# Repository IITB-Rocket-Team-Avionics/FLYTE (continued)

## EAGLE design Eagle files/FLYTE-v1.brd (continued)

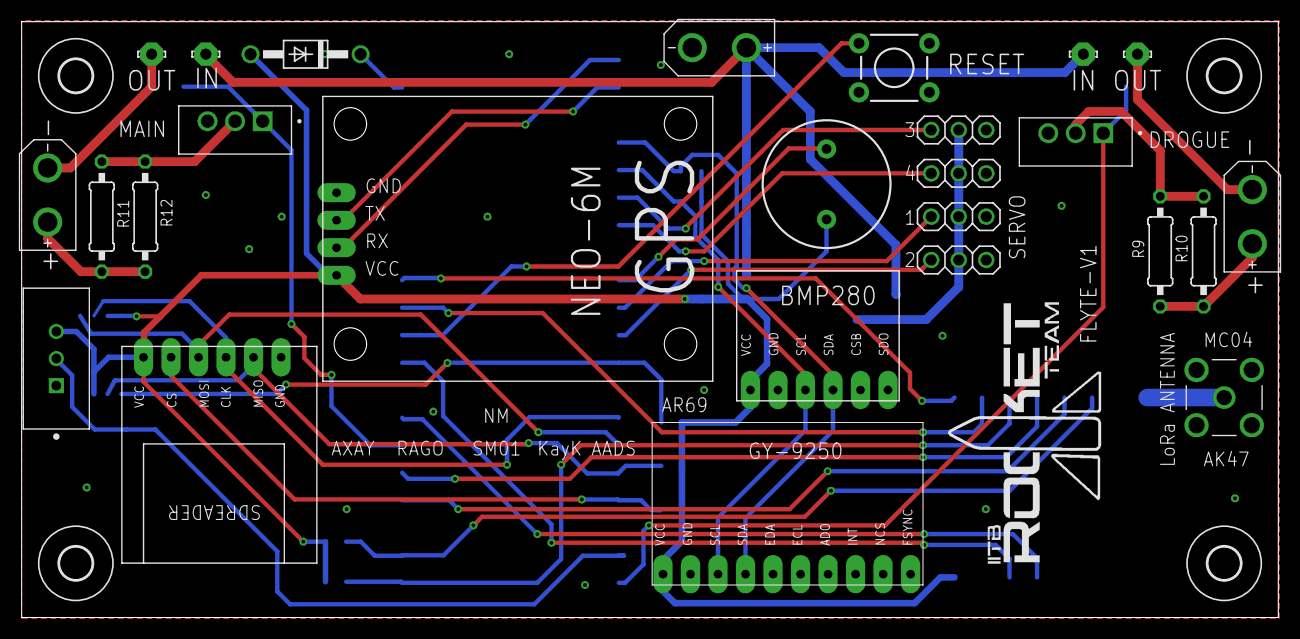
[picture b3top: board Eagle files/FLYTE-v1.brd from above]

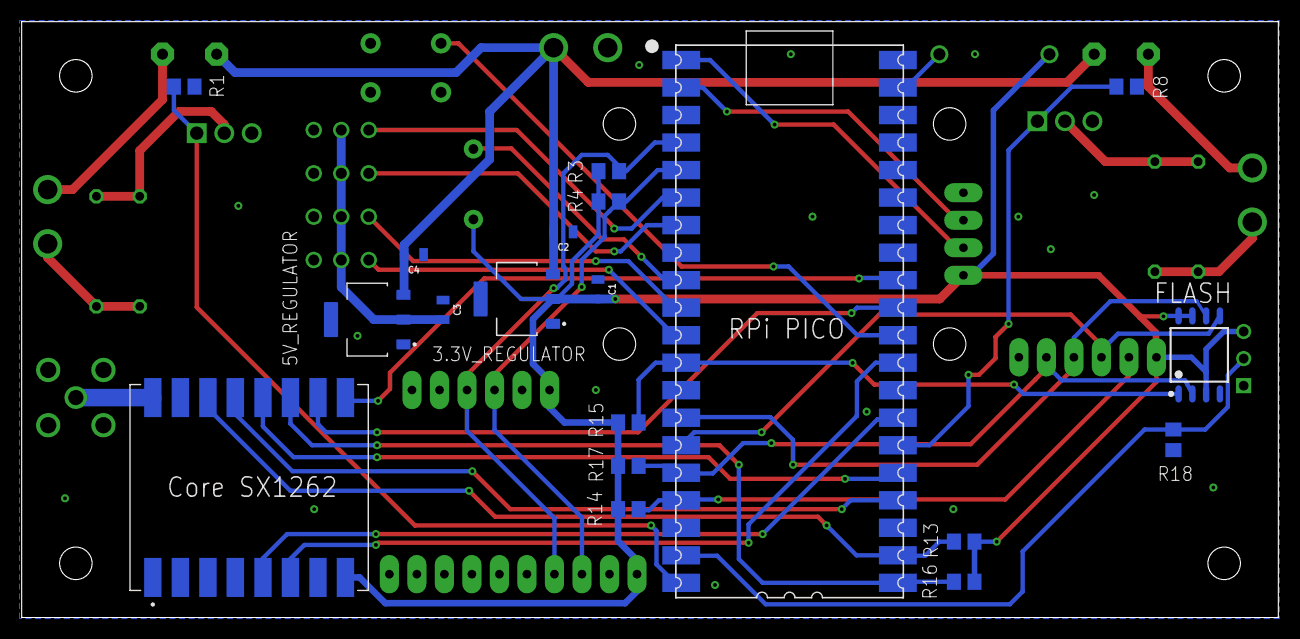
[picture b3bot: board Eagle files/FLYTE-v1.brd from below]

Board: 2 copper layers, 116.0 x 55.0 mm, 49 parts (19 on the bottom side), 38 nets.

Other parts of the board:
U$5, U$6, U$7, U$8: 3,0

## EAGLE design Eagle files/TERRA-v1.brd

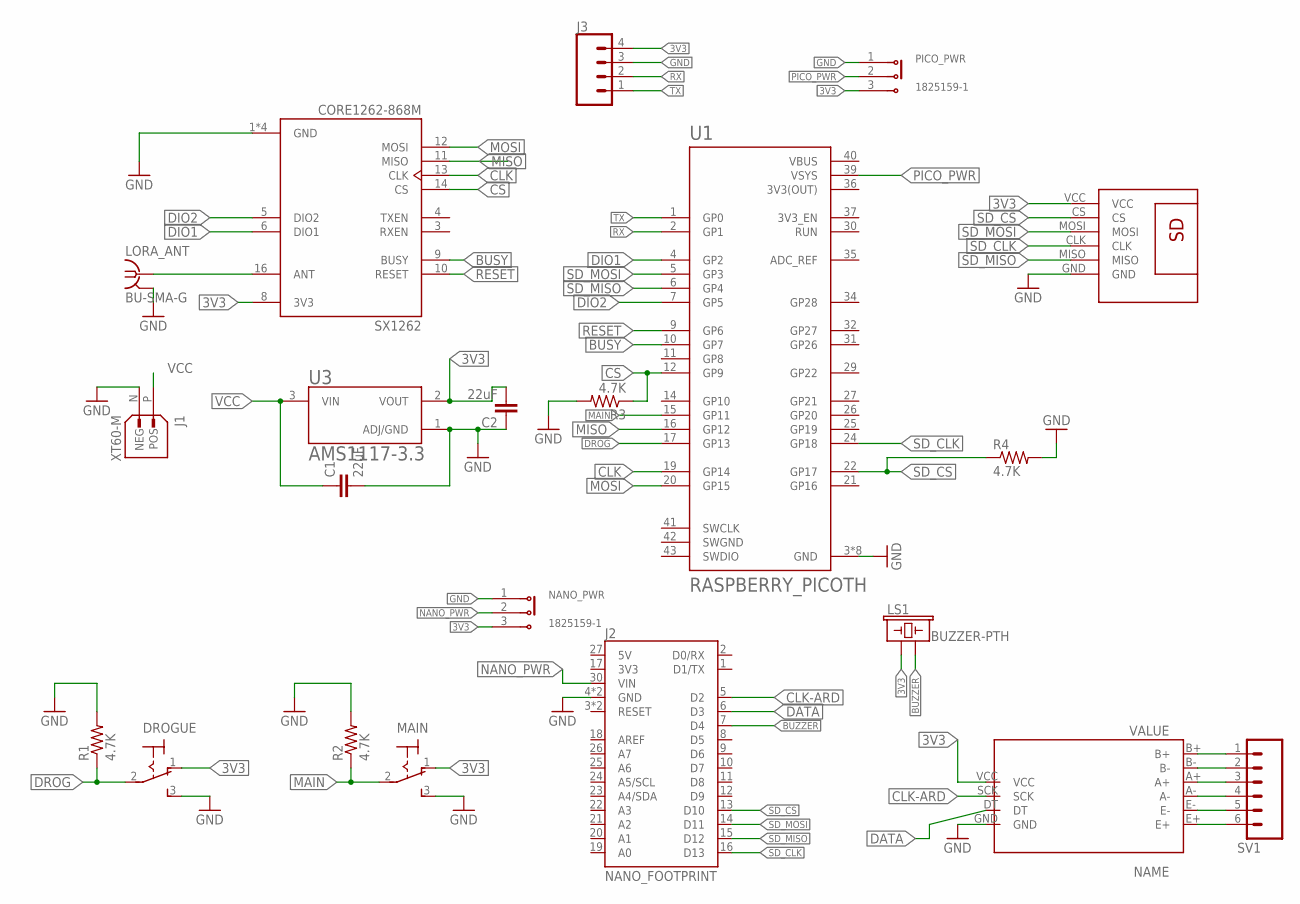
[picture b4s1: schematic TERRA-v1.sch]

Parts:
C1, C2: 22uF; 0805
DROGUE: M9040P
HX711: HX711
J1: XT60-M; AMASS_XT60-M
J2: NANO_FOOTPRINT; NANO
J3: CONN_04PTH; 1X04
LORA_ANT: BU-SMA-G
LS1: BUZZER-PTH; BUZZER-12MM
MAIN: M9040P
NANO_PWR: 1825159-1; SW_1825159-1
PICO_PWR: 1825159-1; SW_1825159-1
R1, R2, R3, R4: 4.7K; R0805
SV1: CONN_06SILK_FEMALE_PTH; 1X06
SX1262: CORE1262-868M; XCVR_CORE1262-868M
U1: RASPBERRY_PICOTH; PICO-PKG-TH
U3: AMS1117-3.3; SOT229P700X180-4N
U$1: SDREADER

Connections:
3V3: C2.2, DROGUE.1 (O), HX711.VCC, J3.4, LS1.+ (1), MAIN.1 (O), NANO_PWR.3, PICO_PWR.3, SX1262.8 (3V3), U3.2 (VOUT), U$1.VCC
3V3(OUT): U1.36 (3V3(OUT))
BUSY: SX1262.9 (BUSY), U1.10 (GP7)
BUZZER: J2.7 (D4), LS1.- (2)
CLK: SX1262.13 (CLK), U1.19 (GP14)
CLK-ARD: HX711.SCK, J2.5 (D2)
CS: R3.1, SX1262.14 (CS), U1.12 (GP9)
DATA: HX711.DT, J2.6 (D3)
DIO1: SX1262.6 (DIO1), U1.4 (GP2)
DIO2: SX1262.5 (DIO2), U1.7 (GP5)
DROG: DROGUE.2, R1.1, U1.17 (GP13)
GND: C1.2, C2.1, DROGUE.3 (S), HX711.GND, J1.N (NEG), J2.4 (GND), J2.29 (GND), J3.3, LORA_ANT.2, LORA_ANT.3 (2), LORA_ANT.4 (2), LORA_ANT.5 (2), MAIN.3 (S), NANO_PWR.1, PICO_PWR.1, R1.2, R2.2, R3.2, R4.2, SX1262.1 (GND), SX1262.2 (GND), SX1262.7 (GND), SX1262.15 (GND), U1.3 (GND), U1.8 (GND), U1.13 (GND), U1.18 (GND), U1.23 (GND), U1.28 (GND), U1.33 (GND), U1.38 (GND), U3.1 (ADJ/GND), U$1.GND
MAIN: MAIN.2, R2.1, U1.15 (GP11)
MISO: SX1262.11 (MISO), U1.16 (GP12)
MOSI: SX1262.12 (MOSI), U1.20 (GP15)
unnamed: LORA_ANT.1, SX1262.16 (ANT)
unnamed: HX711.B+, SV1.1
unnamed: HX711.B-, SV1.2
unnamed: HX711.A+, SV1.3
unnamed: HX711.A-, SV1.4
unnamed: HX711.E-, SV1.5
unnamed: HX711.E+, SV1.6
NANO_PWR: J2.30 (VIN), NANO_PWR.2
PICO_PWR: PICO_PWR.2, U1.39 (VSYS)
RESET: SX1262.10 (RESET), U1.9 (GP6)
RX: J3.2, U1.2 (GP1)
SD_CLK: J2.16 (D13), U1.24 (GP18), U$1.CLK
SD_CS: J2.13 (D10), R4.1, U1.22 (GP17), U$1.CS
SD_MISO: J2.15 (D12), U1.6 (GP4), U$1.MISO
SD_MOSI: J2.14 (D11), U1.5 (GP3), U$1.MOSI
SWGND: U1.42 (SWGND)
TX: J3.1, U1.1 (GP0)
VBUS: U1.40 (VBUS)
VCC: C1.1, J1.P (POS), U3.3 (VIN)

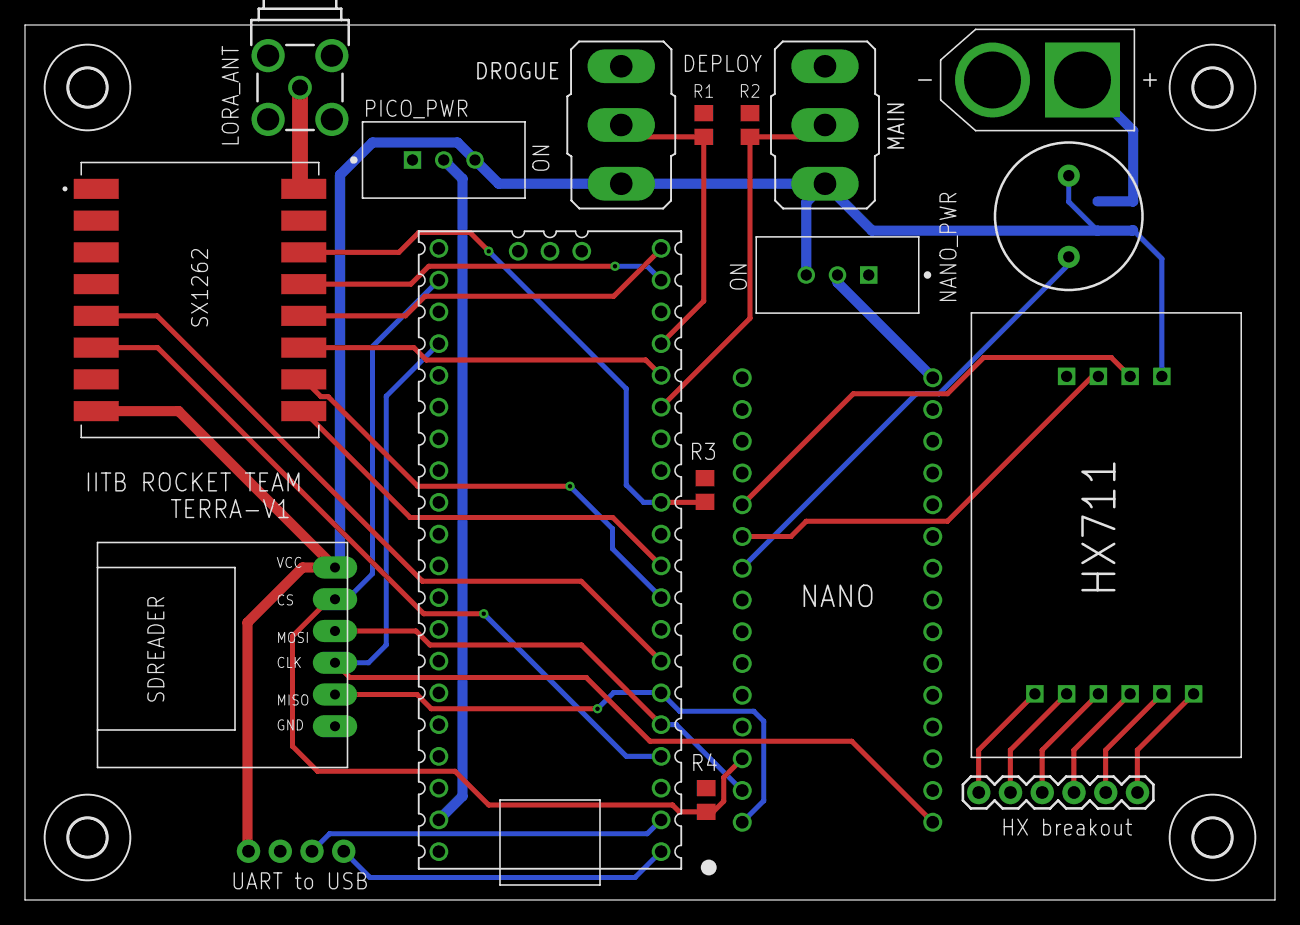
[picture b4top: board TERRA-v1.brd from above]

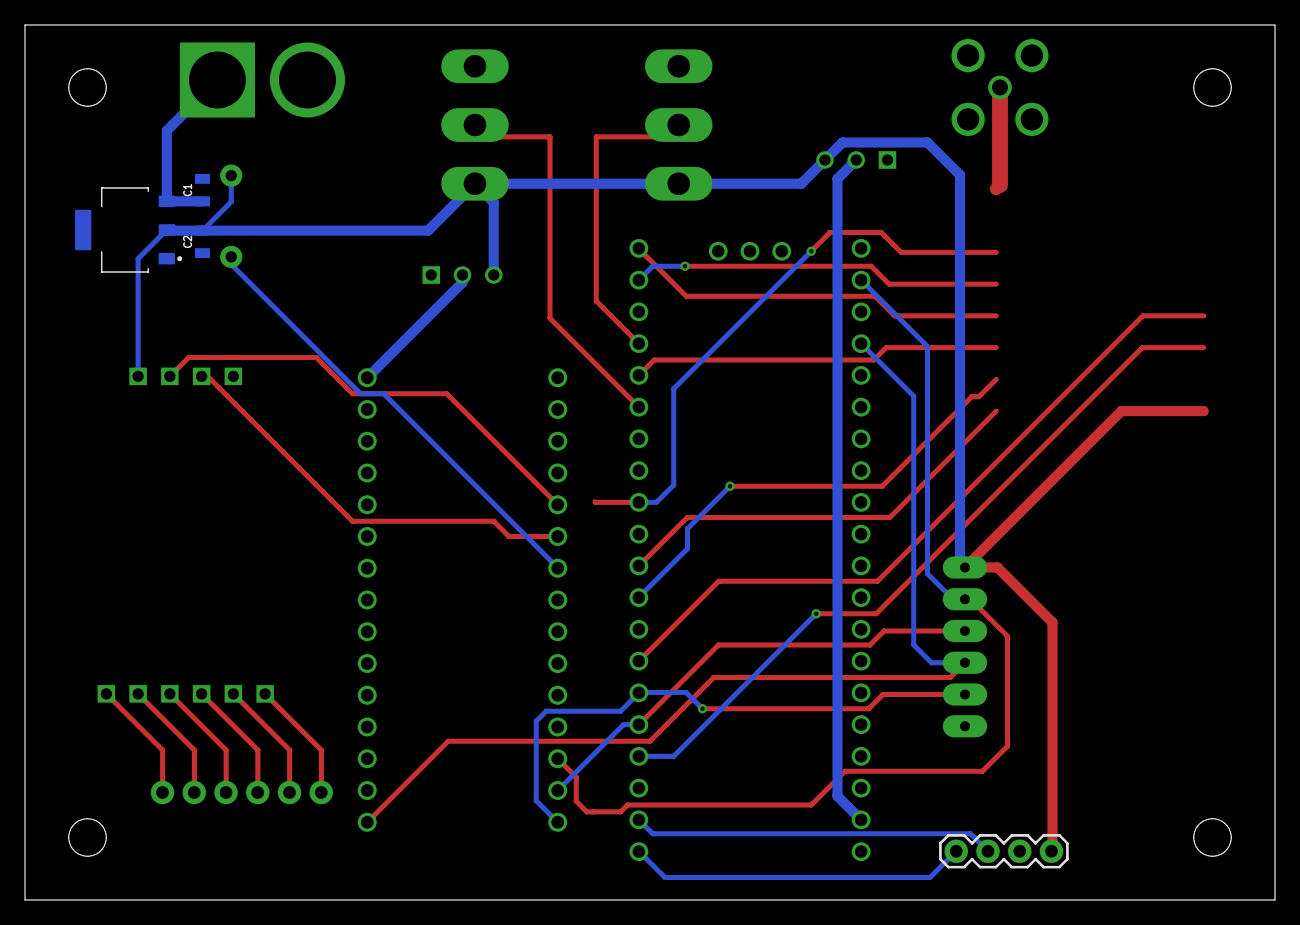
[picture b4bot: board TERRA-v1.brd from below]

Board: 2 copper layers, 100.0 x 70.0 mm, 25 parts (4 on the bottom side), 31 nets.

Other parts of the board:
U$3, U$4, U$5, U$6: 3,0

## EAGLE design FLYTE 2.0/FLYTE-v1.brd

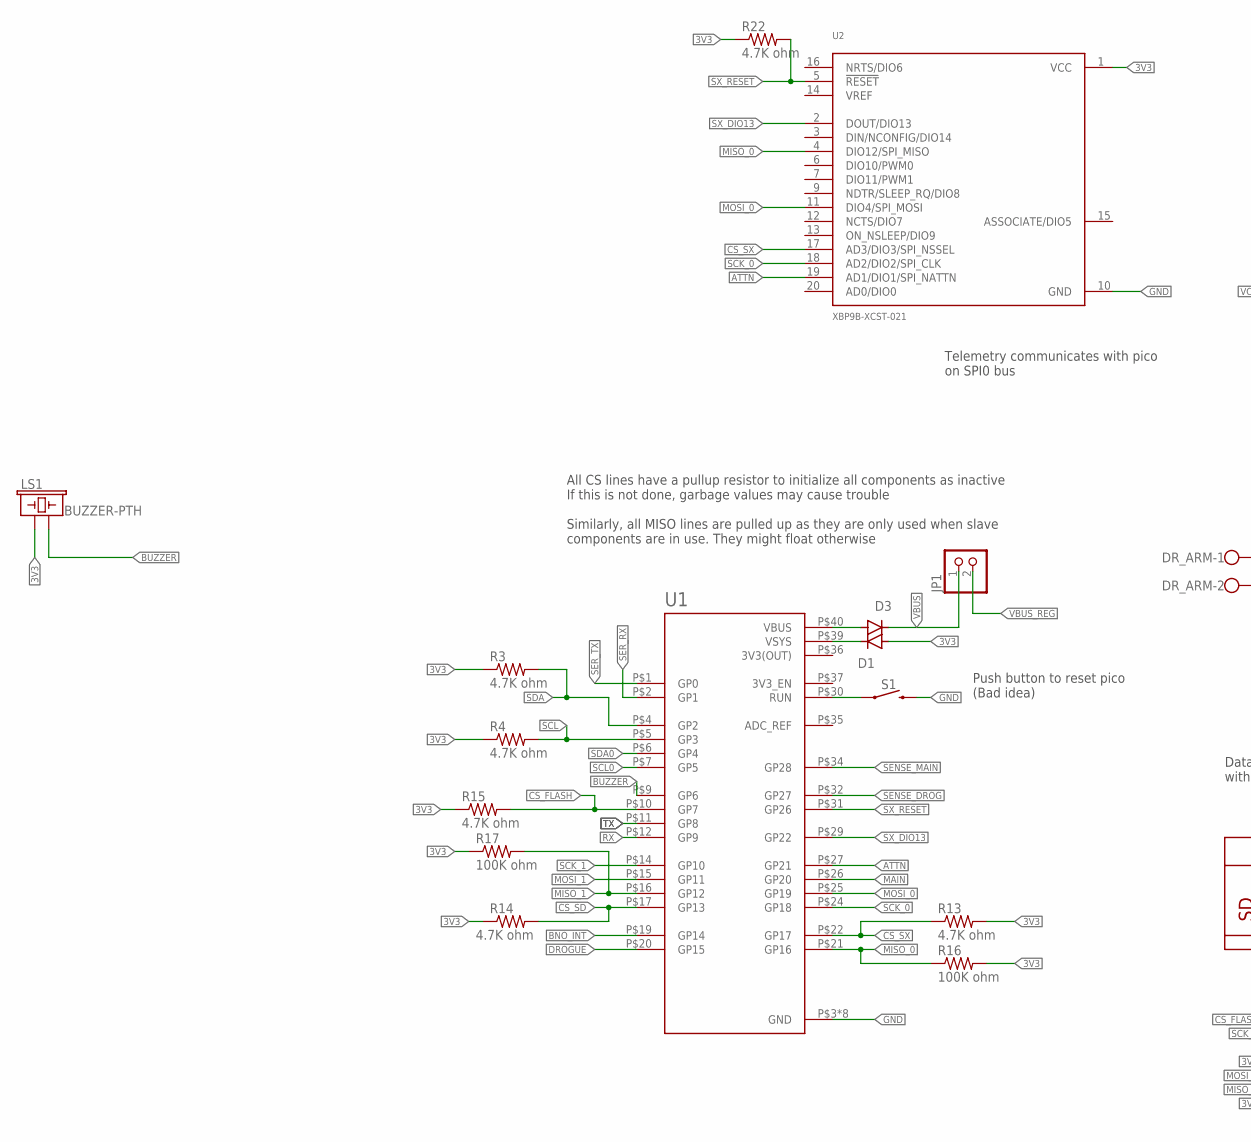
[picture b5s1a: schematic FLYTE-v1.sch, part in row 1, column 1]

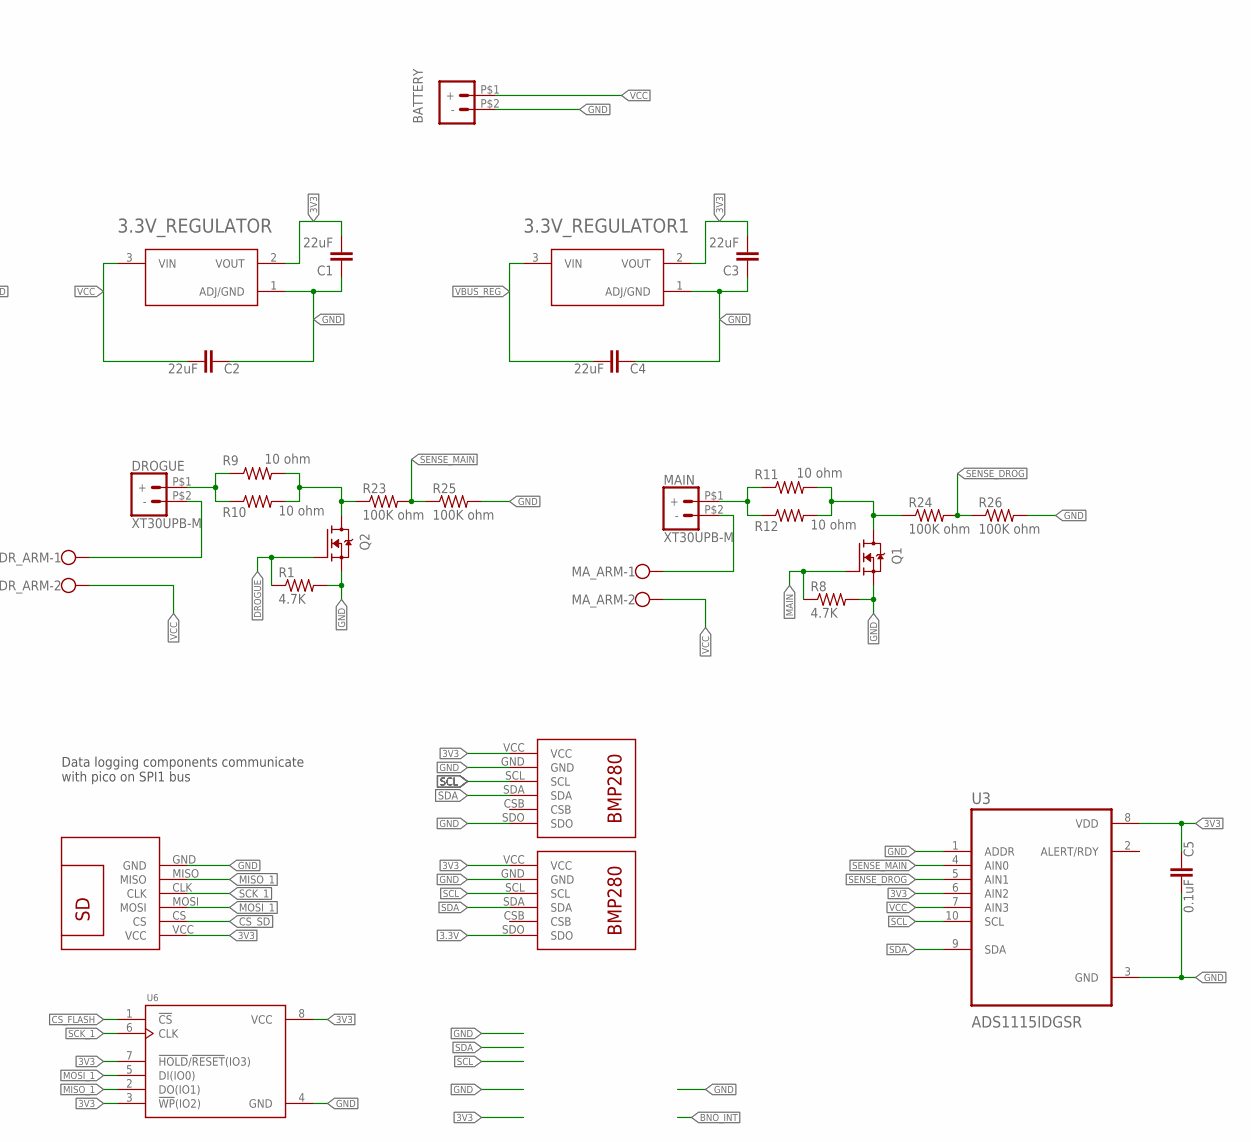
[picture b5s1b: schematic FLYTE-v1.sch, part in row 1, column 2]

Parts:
3.3V_REGULATOR, 3.3V_REGULATOR1: AMS1117-3.3; SOT229P700X180-4N
BATTERY: XT30UPB-M
C1, C2, C3, C4: 22uF; 0805
C5: 0.1uF; 0805
D1, D3: 1N4004; DO41-10
DROGUE: XT30UPB-M
DR_ARM: W237-102
JP1: PINHD-1X2; 1X02
LS1: BUZZER-PTH; BUZZER-12MM
MAIN: XT30UPB-M
MA_ARM: W237-102
Q1, Q2: IRF540NPBF; TO254P1054X469X1930-3
R1, R8: 4.7K; R0805
R3, R4, R13, R14, R15, R22: 4.7K ohm; R0805
R9, R10, R11, R12: 10 ohm; 0207/10
R16, R17, R23, R24, R25, R26: 100K ohm; R0805
S1: MOMENTARY-SWITCH-SPST-PTH-6.0MM; TACTILE_SWITCH_PTH_6.0MM
U1: RASPBERRY_PICO-NO_DEBUG; PICO-PKG-NO_DEBUG
U2: XBP9B-XCST-021; DIP2200W51P200L3294H279Q20P
U3: ADS1115IDGSR; SOP50P490X110-10N
U6: W25Q32JVSSIQ; SOIC127P790X216-8N
U$1, U$2: BMP280
U$3: SDREADER

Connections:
3.3V: U$2.SDO
3V3: 3.3V_REGULATOR.2 (VOUT), 3.3V_REGULATOR1.2 (VOUT), C1.2, C3.2, C5.1, D1.A, LS1.+ (1), R3.1, R4.1, R13.2, R14.1, R15.1, R16.2, R17.1, R22.1, U2.1 (VCC), U3.6 (AIN2), U3.8 (VDD), U6.3 (!WP!(IO2)), U6.7 (!HOLD!/!RESET!(IO3)), U6.8 (VCC), U$1.VCC, U$2.VCC, U$3.VCC
3V3(OUT): U1.P$36 (3V3(OUT))
ATTN: U1.P$27 (GP21), U2.19 (AD1/DIO1/SPI_NATTN)
BNO_INT: U1.P$19 (GP14)
BUZZER: LS1.- (2), U1.P$9 (GP6)
CS_FLASH: R15.2, U1.P$10 (GP7), U6.1 (!CS)
CS_SD: R14.2, U1.P$17 (GP13), U$3.CS
CS_SX: R13.1, U1.P$22 (GP17), U2.17 (AD3/DIO3/SPI_NSSEL)
DROGUE: Q2.1 (G), R1.1, U1.P$20 (GP15)
GND: 3.3V_REGULATOR.1 (ADJ/GND), 3.3V_REGULATOR1.1 (ADJ/GND), BATTERY.P$2 (-), C1.1, C2.1, C3.1, C4.1, C5.2, Q1.3 (S), Q2.3 (S), R1.2, R8.2, R25.2, R26.2, S1.3 (2), U1.P$3 (GND), U1.P$8 (GND), U1.P$13 (GND), U1.P$18 (GND), U1.P$23 (GND), U1.P$28 (GND), U1.P$33 (GND), U1.P$38 (GND), U2.10 (GND), U3.1 (ADDR), U3.3 (GND), U6.4 (GND), U$1.GND, U$1.SDO, U$2.GND, U$3.GND
MAIN: Q1.1 (G), R8.1, U1.P$26 (GP20)
MISO_0: R16.1, U1.P$21 (GP16), U2.4 (DIO12/SPI_MISO)
MISO_1: R17.2, U1.P$16 (GP12), U6.2 (DO(IO1)), U$3.MISO
MOSI_0: U1.P$25 (GP19), U2.11 (DIO4/SPI_MOSI)
MOSI_1: U1.P$15 (GP11), U6.5 (DI(IO0)), U$3.MOSI
unnamed: D1.C, U1.P$39 (VSYS)
unnamed: DROGUE.P$2 (-), DR_ARM.1
unnamed: MAIN.P$1 (+), R11.1, R12.1
unnamed: DROGUE.P$1 (+), R9.1, R10.1
unnamed: S1.1, U1.P$30 (RUN)
unnamed: Q2.2 (D), R9.2, R10.2, R23.1
unnamed: Q1.2 (D), R11.2, R12.2, R24.1
unnamed: MAIN.P$2 (-), MA_ARM.1
unnamed: D3.A, U1.P$40 (VBUS)
RX: U1.P$12 (GP9)
SCK_0: U1.P$24 (GP18), U2.18 (AD2/DIO2/SPI_CLK)
SCK_1: U1.P$14 (GP10), U6.6 (CLK), U$3.CLK
SCL: R4.2, U1.P$5 (GP3), U3.10 (SCL), U$1.SCL, U$2.SCL
SCL0: U1.P$7 (GP5)
SDA: R3.2, U1.P$4 (GP2), U3.9 (SDA), U$1.SDA, U$2.SDA
SDA0: U1.P$6 (GP4)
SENSE_DROG: R24.2, R26.1, U1.P$32 (GP27), U3.5 (AIN1)
SENSE_MAIN: R23.2, R25.1, U1.P$34 (GP28), U3.4 (AIN0)
SER_RX: U1.P$2 (GP1)
SER_TX: U1.P$1 (GP0)
SX_DIO13: U1.P$29 (GP22), U2.2 (DOUT/DIO13)
SX_RESET: R22.2, U1.P$31 (GP26), U2.5 (!RESET)
TX: U1.P$11 (GP8)
VBUS: D3.C, JP1.1
VBUS_REG: 3.3V_REGULATOR1.3 (VIN), C4.2, JP1.2
VCC: 3.3V_REGULATOR.3 (VIN), BATTERY.P$1 (+), C2.2, DR_ARM.2, MA_ARM.2, U3.7 (AIN3)

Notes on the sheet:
Telemetry communicates with pico on SPI0 bus
Data logging components communicate with pico on SPI1 bus
All CS lines have a pullup resistor to initialize all components as inactive If this is not done, garbage values may cause trouble Similarly, all MISO lines are pulled up as they are only used when slave components are in use. They might float otherwise
Push button to reset pico (Bad idea)

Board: 2 copper layers, 44 parts (0 on the bottom side), 33 nets, no tracks yet.

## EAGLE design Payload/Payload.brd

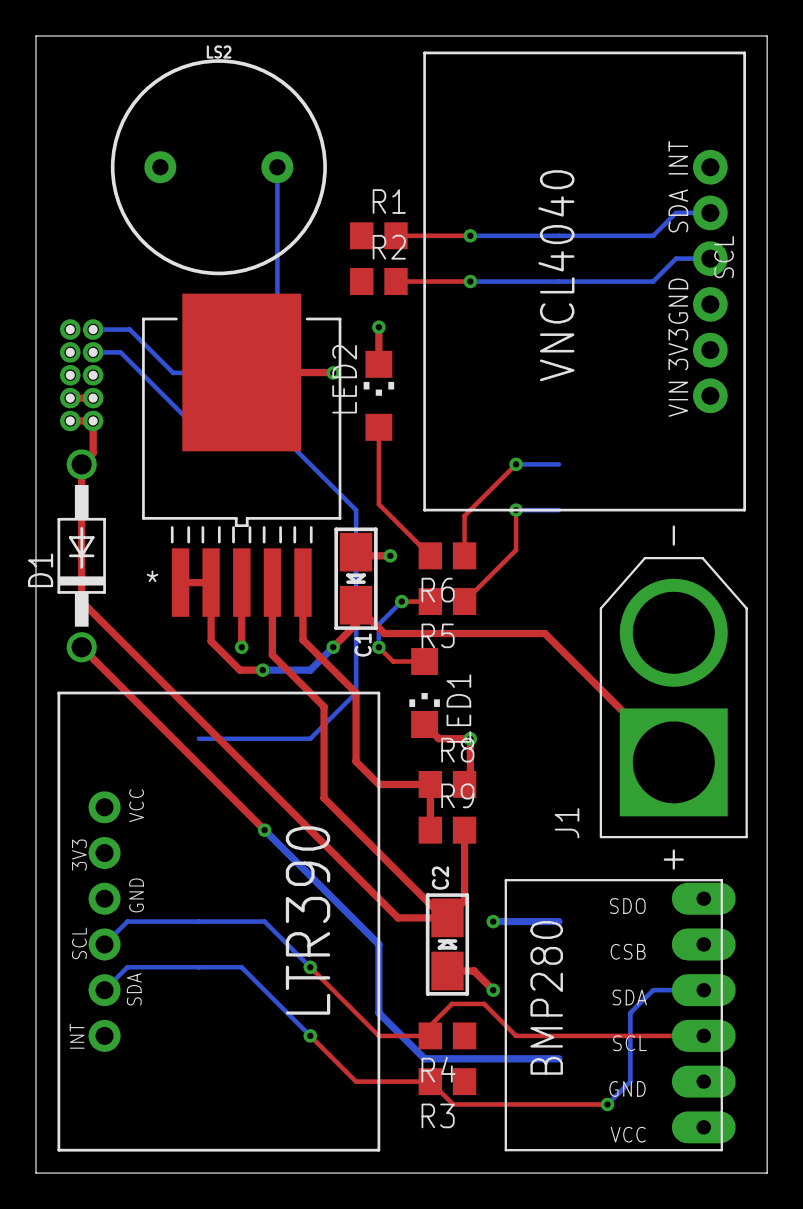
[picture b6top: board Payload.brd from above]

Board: 2 copper layers, 40.6 x 63.2 mm, 22 parts (1 on the bottom side), 17 nets.

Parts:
C1, C2: 10 uF; EIA3216-18/A-W
D1: 1N4004; DO41-10
J1: XT60-M; AMASS_XT60-M
LED1, LED2: CHIPLED_1206
LS2: BUZZER-PTH; BUZZER-12MM
R1, R2, R3, R4: 4.7K ohm; R0805
R5, R6: 330 ohm; R0805
R8: 100k ohm; R0805
R9: 301k ohm; R0805
U1: PICO-PKG-NO_DEBUG
U2: MIC29302WU-TRTO-263-5_MCH-M; TO-263-5_MCH-M
U$1: VCNL4040
U$3: BMP280
U$4: LTR390
U$5, U$6: 1X5

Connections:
3V3: R1.1, R2.1, R3.1, R4.1, U1.P$36, U$1.VIN, U$3.VCC, U$4.VCC
5V: C2.+, D1.A, R9.2, U2.4, U$5.5, U$6.1
7.4V: C1.+, J1.P, U2.1, U2.2
BUZZER: LS2.+, U1.P$9
GND: C1.-, C2.-, J1.N, LED1.C, LED2.C, LS2.-, R8.2, U1.P$3, U1.P$8, U1.P$13, U1.P$18, U1.P$23, U1.P$28, U1.P$33, U1.P$38, U2.3, U2.6, U$1.GND, U$3.GND, U$4.GND, U$5.4, U$6.2
unnamed: D1.C, U1.P$39
unnamed: R5.1, U1.P$27
unnamed: LED2.A, R6.2
unnamed: LED1.A, R5.2
unnamed: R6.1, U1.P$26
unnamed: R8.1, R9.1, U2.5
RX: U1.P$17, U$5.1
SCL0: R2.2, U1.P$22, U$1.SCL
SCL1: R4.2, U1.P$5, U$3.SCL, U$4.SCL
SDA0: R1.2, U1.P$21, U$1.SDA
SDA1: R3.2, U1.P$4, U$3.SDA, U$4.SDA
TX: U1.P$16, U$5.2
